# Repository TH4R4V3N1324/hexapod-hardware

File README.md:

# hexapod-hardware

Open-source hardware for 3D-printed six-legged walking robots. The repo has the CAD (STEP for editing, STL for printing), bills of materials, print lists and assembly docs. Shared electronics, including the [leg hub](electronics/leg-hub/) power and data board, are in [`electronics/`](electronics/).

## Variants

| Variant | Key hardware | Status |
|---|---|---|
| [Explorer](explorer/) | ST3215 servos, Raspberry Pi 5, lidar | v0.2, in development |

Each variant's folder has its own README, [print list](explorer/print-list.md), BOM and changelog.

## Licences

This repository uses two licences:

- **CAD, STLs and documentation**: [Creative Commons Attribution-ShareAlike 4.0 International (CC BY-SA 4.0)](LICENSE)
- **PCB designs** (everything in [`electronics/`](electronics/)): [CERN Open Hardware Licence Version 2 – Weakly Reciprocal (CERN-OHL-W-2.0)](electronics/LICENSE)

The source for this design is at <https://github.com/TH4R4V3N1324/hexapod-hardware>.

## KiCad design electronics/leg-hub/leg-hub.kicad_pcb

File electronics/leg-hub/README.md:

# Leg hub

> ⚠️ **v0.1: under development.** The design may change, and the board hasn't been fully verified. Check everything against the schematic before you power it up.

The leg hub is the power and data board for one side of the hexapod. Every robot uses **two identical boards**, one for the left legs and one for the right. Each board:

- **Distributes power and servo data to three legs** through individually fused connectors.
- **Makes 5 V / 5 A** for the Raspberry Pi, sensors and other peripherals.
- **Measures current, voltage and power** for its side with an INA226 on I²C.
- **Switches servo power** with a fail-safe high-side switch that needs both a GPIO enable and a closed kill loop.
- **Switches itself fully on and off** from one small latching switch.

## Specifications

| | |
|---|---|
| Input | 3S LiPo (9.0–12.6 V) via XT30 |
| Board switch | P-FET, about 15 A per board |
| Leg outputs | 3 × fused 5 A (mini blade), battery voltage |
| 5 V output | 5 A synchronous buck (TPS56528), 650 kHz |
| Current sense | INA226, 2 mΩ shunt, about 40 A full scale |
| Host logic | 3.3 V (default) or 5 V, selected by JP3 |
| Input protection | SMBJ13A TVS, 220 µF + 470 µF bulk |
| Mounting | 4 × M3 |

## How the board works

<p align="center">
  <picture>
    <source media="(prefers-color-scheme: dark)" srcset="images/power-flow-dark.png">
    
  </picture>
</p>

Servo data comes in on BUS_IN (J6) and is shared to the data pin of all three leg connectors.

1. **Board switch (Q3).** The board stays off until J11 is shorted. If the switch is open or a wire breaks, R18 turns Q3 off and everything on that board loses power: buck, Pi and servos. Only about 1 mA flows through the switch, so any small latching switch works.
2. **Current sense (U2, R1).** The shunt sits after Q3, so the INA226 measures everything the board draws: servos plus 5 V load.
3. **Servo switch (Q1).** Servo power comes on only when **SERVO_EN is high and the kill loop (J8) is closed**. R5 holds the servos off while the host GPIO floats during boot.
4. **Leg outputs.** Each leg has its own 5 A blade fuse, matched to the roughly 3 A-per-pin rating of the servo connectors (brief peaks are fine).
5. **Servo data.** Data from the bus servo adapter is shared to all three legs, each through a 22 Ω series resistor and an ESD clamp.
6. **Adapter power.** J6 pin 2 feeds the switched servo rail to the bus servo adapter through a Schottky diode (D7), to power the adapter's own chips. The diode stops the adapter feeding power back into the board. This feed isn't fused, so don't power servos or anything else through the adapter. Servo power goes to the legs only through J3–J5.

## Connectors

| Ref | Name | Type | Pinout / use |
|---|---|---|---|
| J1 | Battery in | Amass XT30PW-M | 3S pack. Check polarity against your lead. |
| J2 | 5 V out | Molex Micro-Fit 3.0, 2-pin | 5 V / 5 A for the Pi, sensors or other peripherals |
| J3–J5 | LEG1–LEG3 | Molex SPOX 5267-03A (2.5 mm) | 1 DATA · 2 V+ (fused) · 3 GND. Same pinout as the servos, so a straight-through servo cable works. |
| J6 | BUS_IN | Molex SPOX 5267-03A | To the bus servo adapter: 1 DATA · 2 V out to the adapter (servo rail through D7, for the adapter's chips only) · 3 GND |
| J7 | CTRL | JST PH, 5-pin | To the host (Pi / ESP32 / Pico / Arduino): 1 SDA · 2 SCL · 3 INA ALERT (open-drain) · 4 SERVO_EN · 5 GND |
| J8 | KILL | JST PH, 2-pin | Normally-closed kill loop. Open = servos off. |
| J9, J10 | QWIIC | JST SH, 4-pin | Qwiic / STEMMA QT: 1 GND · 2 3V3 · 3 SDA · 4 SCL. The two ports are wired in parallel for daisy-chaining. |
| J11 | PWR_SW | JST PH, 4-pin | Main switch and its light: 1–2 switch (short to turn the board on) · 3 LED+ · 4 LED− (GND). LED+ is live only while the board is on, through R20 (1 kΩ). |

## Jumpers

| Ref | Name | Default | Purpose |
|---|---|---|---|
| JP1 | ADDR | Open (left) / **bridged (right)** | INA226 address: open = `0x40`, bridged = `0x41` |
| JP2 | KILL_BYP | Open | Bypasses the kill loop. Use it on the bench only. |
| JP3 | LOGIC_V | Cap on 1–2 | INA226 logic level: 1–2 = 3.3 V host, 2–3 = 5 V host. Must be 1–2 when using Qwiic. |
| JP4 | QW_PWR | Open | Feeds Qwiic 3V3 from this board. Leave it open with a Pi, and bridge it only if nothing upstream powers the chain. |
| JP5 | I2C_PU | Open | On-board 4.7 kΩ I²C pull-ups. Leave them open with a Pi, which already has pull-ups. |
| JP6 | PWR_BYP | Open | Keeps the board always on, without a switch. Bench use only. |

## Left vs right board

The two boards are the same PCB. The only difference is the INA226 address, so both can share one I²C bus:

| | Left | Right |
|---|---|---|
| JP1 | Open → `0x40` | Bridged → `0x41` |

Either board's 5 V output can power the Pi or peripherals.

## Wiring the pair

- **Battery:** split the pack to both boards' J1 with **equal-length wires**.
- **Power switch:** wire one latching switch to **both boards' J11 pins 1–2 in parallel** for a single hard power-off. There's no soft shutdown.
- **Switch light:** wire an illuminated switch's LED, or any other indicator, to J11 pins 3 (+) and 4 (−) of **one** board. R20 (1 kΩ) suits a bare LED and keeps a shorted wire harmless. A 12 V-rated LED with its own resistor will light more dimly, so change R20 to a lower value or 0 Ω if you want it brighter.
- **E-stop:** use a button with two normally-closed contacts and wire one contact across each board's J8.
- **SERVO_EN:** drive it from a Pi GPIO that defaults to **pull-down at boot** (GPIO9–27), so the servos stay off while the Pi starts.
- **I²C:** chain Pi → left board → right board → IMU and so on, through J7 or the Qwiic ports.
- **Never tie the two 5 V rails together.** Watch for this through USB VBUS if the Pi and a USB device are powered from different boards.

## Before first power-up

- [ ] JP1 set correctly for left / right
- [ ] JP3 on 1–2 for a Pi or other 3.3 V host
- [ ] JP2, JP4, JP5 and JP6 open (unless you need them, as described above)
- [ ] XT30 and bus adapter cable pin 1 checked against your leads
- [ ] Fuses F1–F3 fitted (5 A mini blade)

## Files

| File | Contents |
|---|---|
| `leg-hub.kicad_pro` | KiCad project. Open this one. |
| `leg-hub.kicad_sch` | Schematic |
| `leg-hub.kicad_pcb` | PCB layout |
| `fp-lib-table`, `hexapod.pretty/` | Project footprint library (custom TDSON-8 footprint for Q3) |
| `3dmodels/` | 3D models for the XT30, Micro-Fit and SPOX connectors, and a simplified model of Q3's PG-TDSON-8 package |
| `images/` | Diagrams used in this README |

The project needs **KiCad 10** or newer. Every other symbol, footprint and 3D model comes from the standard KiCad libraries.

## Licence

CERN Open Hardware Licence v2, Weakly Reciprocal (CERN-OHL-W). See [`../LICENSE`](../LICENSE).

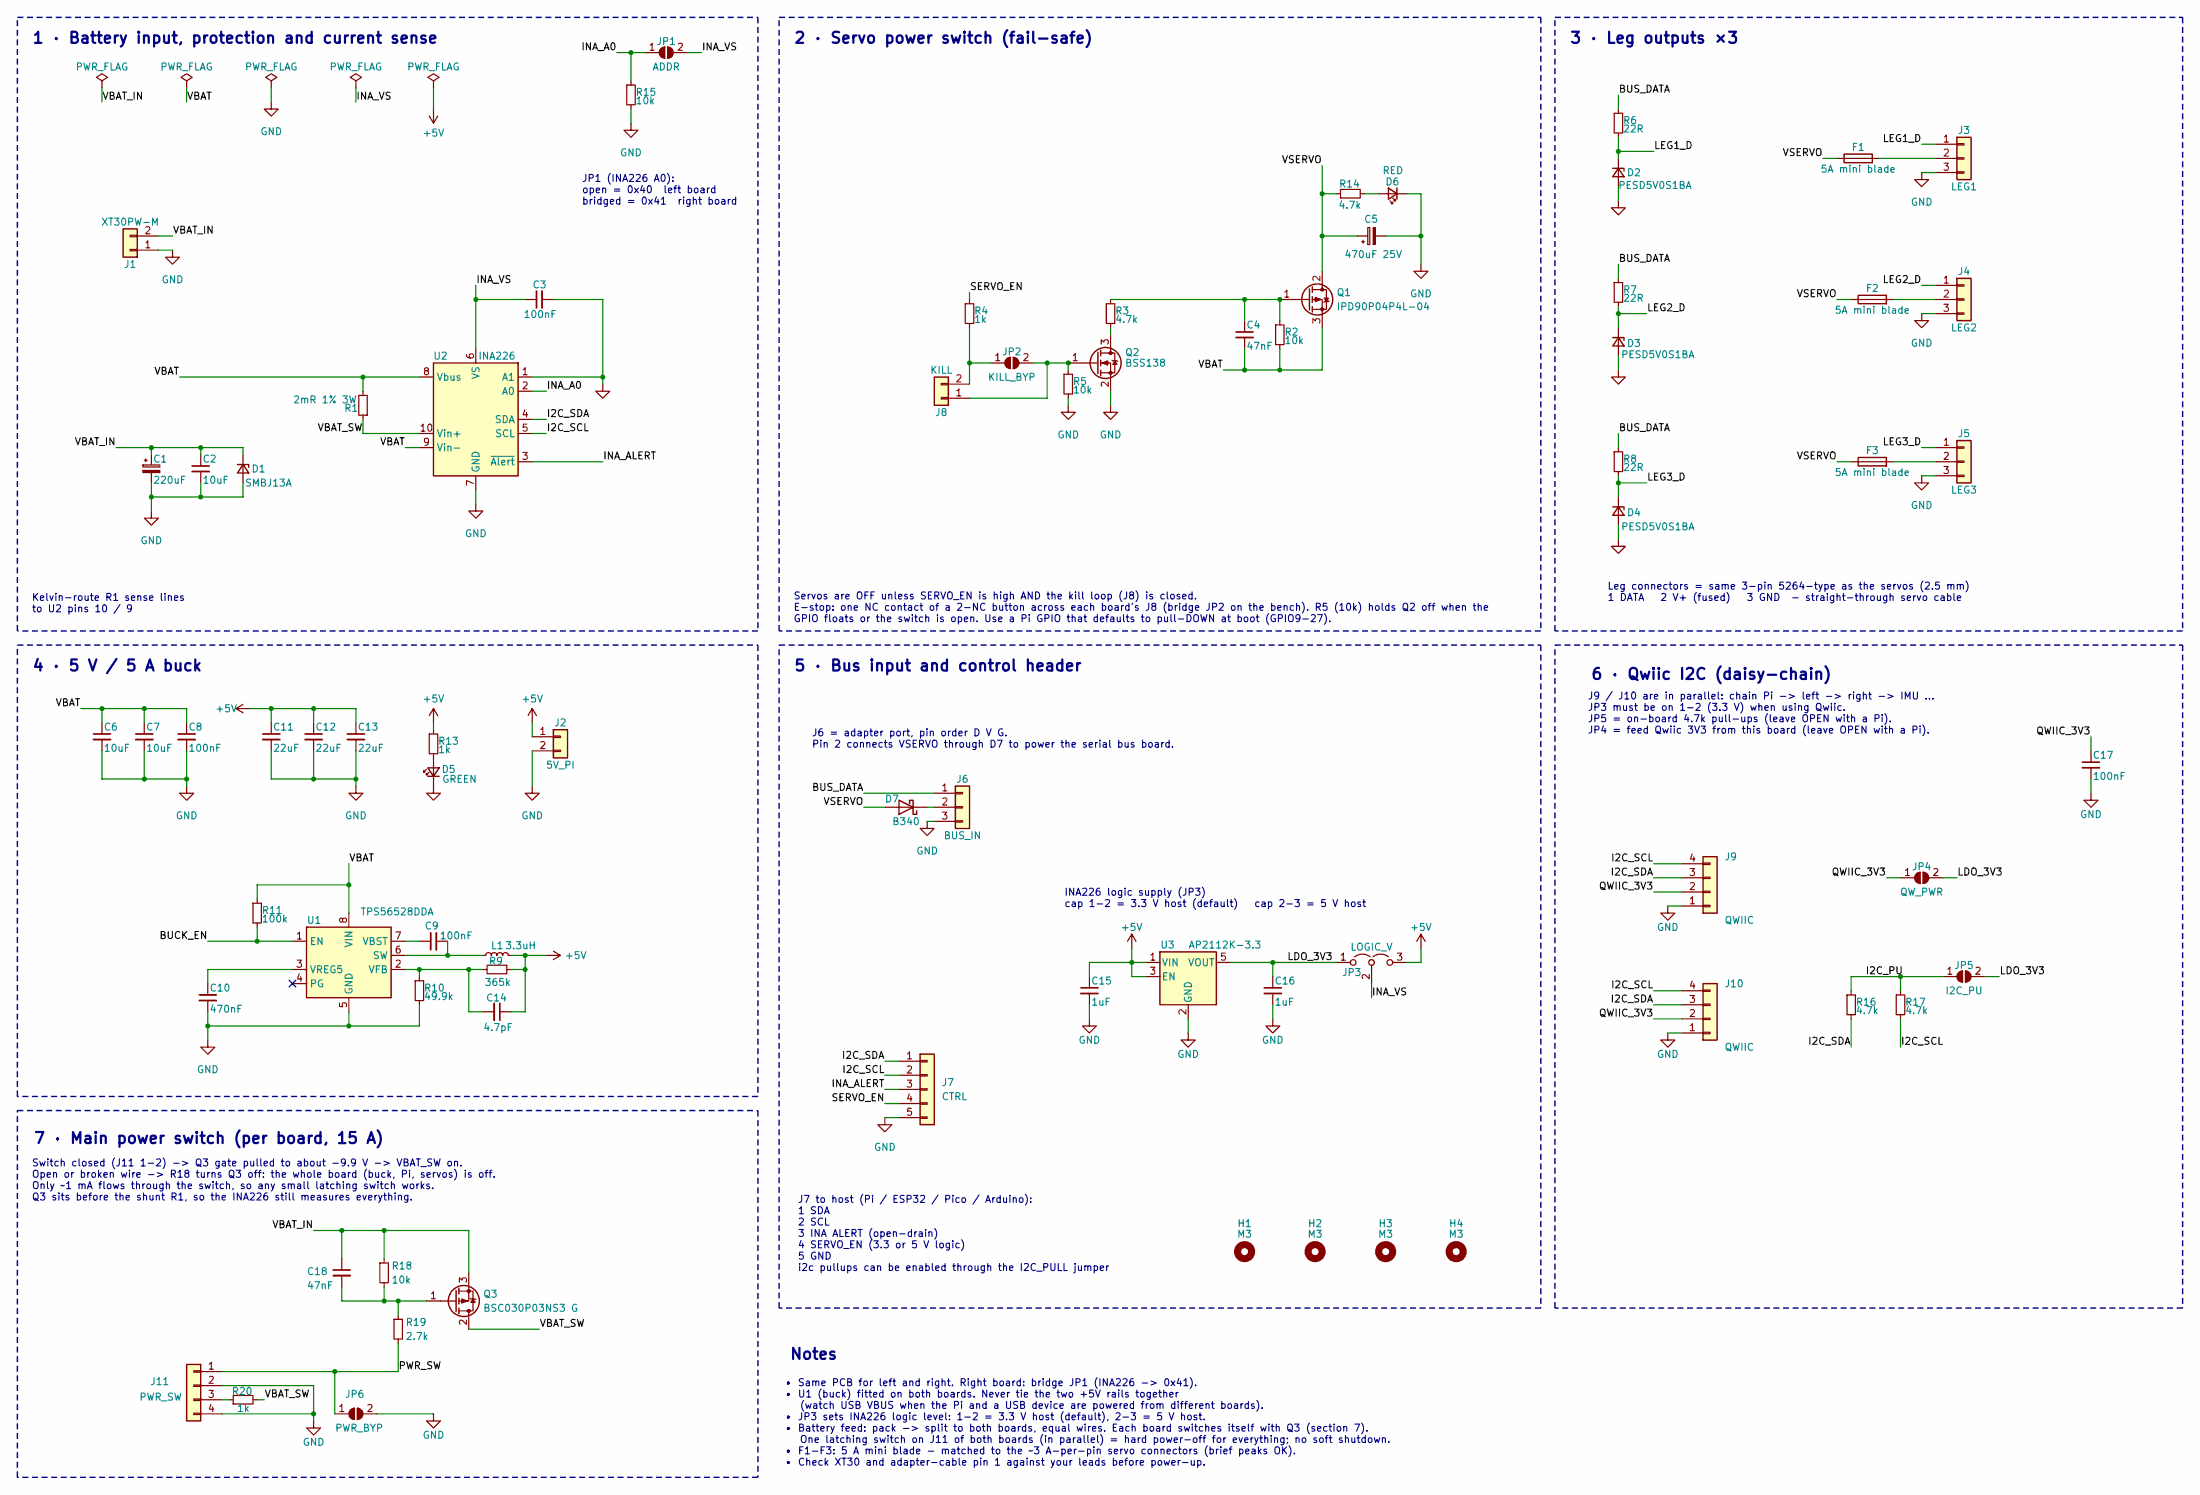
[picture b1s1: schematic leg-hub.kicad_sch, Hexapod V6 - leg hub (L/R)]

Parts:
C1: 220uF; CP_Elec_8x10.5
C2, C6, C7: 10uF; C_1206_3216Metric
C3, C8, C9, C17: 100nF; C_0603_1608Metric
C4, C18: 47nF; C_0603_1608Metric
C5: 470uF 25V; CP_Elec_10x10.5
C10: 470nF; C_0603_1608Metric
C11, C12, C13: 22uF; C_1206_3216Metric
C14: 4.7pF; C_0603_1608Metric
C15, C16: 1uF; C_0603_1608Metric
D1: SMBJ13A; D_SMB; MPN SMBJ13A
D2, D3, D4: PESD5V0S1BA; D_SOD-323; MPN PESD5V0S1BA
D5: GREEN; LED_0603_1608Metric
D6: RED; LED_0603_1608Metric
D7: B340; D_SMC
F1, F2, F3: 5A mini blade; Fuseholder_Blade_Mini_Keystone_3568; MPN Keystone 3568 + 5 A mini blade fuse
H1, H2, H3, H4: M3; MountingHole_3.2mm_M3
J1: XT30PW-M; AMASS_XT30PW-M_1x02_P2.50mm_Horizontal; MPN Amass XT30PW-M
J2: 5V_PI; Molex_Micro-Fit_3.0_43650-0200_1x02_P3.00mm_Horizontal; MPN Molex 43650-0200
J3: LEG1; Molex_SPOX_5267-03A_1x03_P2.50mm_Vertical; MPN Molex 5267-03A
J4: LEG2; Molex_SPOX_5267-03A_1x03_P2.50mm_Vertical; MPN Molex 5267-03A
J5: LEG3; Molex_SPOX_5267-03A_1x03_P2.50mm_Vertical; MPN Molex 5267-03A
J6: BUS_IN; Molex_SPOX_5267-03A_1x03_P2.50mm_Vertical; MPN Molex 5267-03A
J7: CTRL; JST_PH_S5B-PH-K_1x05_P2.00mm_Horizontal
J8: KILL; JST_PH_S2B-PH-K_1x02_P2.00mm_Horizontal; MPN JST S2B-PH-K-S
J9, J10: QWIIC; JST_SH_SM04B-SRSS-TB_1x04-1MP_P1.00mm_Horizontal; MPN JST SM04B-SRSS-TB(LF)(SN) (LCSC C160404)
J11: PWR_SW; JST_PH_S4B-PH-K_1x04_P2.00mm_Horizontal
JP1: ADDR; SolderJumper-2_P1.3mm_Open_RoundedPad1.0x1.5mm
JP2: KILL_BYP; SolderJumper-2_P1.3mm_Open_RoundedPad1.0x1.5mm
JP3: LOGIC_V; PinHeader_1x03_P2.54mm_Vertical
JP4: QW_PWR; SolderJumper-2_P1.3mm_Open_RoundedPad1.0x1.5mm
JP5: I2C_PU; SolderJumper-2_P1.3mm_Open_RoundedPad1.0x1.5mm
JP6: PWR_BYP; SolderJumper-2_P1.3mm_Open_RoundedPad1.0x1.5mm
L1: 3.3uH; L_Coilcraft_XAL7030-332; MPN Coilcraft XAL7030-332
Q1: IPD90P04P4L-04; TO-252-3_TabPin2; MPN IPD90P04P4L-04
Q2: BSS138; SOT-23; MPN BSS138
Q3: BSC030P03NS3 G; TDSON-8_GDS; MPN BSC030P03NS3 G
R1: 2mR 1% 3W; R_2512_6332Metric
R2, R5, R15, R18: 10k; R_0603_1608Metric
R3, R14, R16, R17: 4.7k; R_0603_1608Metric
R4, R13: 1k; R_0603_1608Metric
R6, R7, R8: 22R; R_0603_1608Metric
R9: 365k; R_0603_1608Metric
R10: 49.9k; R_0603_1608Metric
R11: 100k; R_0603_1608Metric
R19: 2.7k; R_0603_1608Metric
R20: 1k; R_1206_3216Metric
U1: TPS56528DDA; Texas_HSOP-8-1EP_3.9x4.9mm_P1.27mm_ThermalVias; MPN TPS56528DDAR
U2: INA226; TSSOP-10_3x3mm_P0.5mm; MPN INA226AIDGSR
U3: AP2112K-3.3; SOT-23-5

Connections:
+5V: C11.1, C12.1, C13.1, C14.1, C15.1, J2.1, JP3.3 (B), L1.2, R9.1, R13.1, U3.1 (VIN), U3.3 (EN)
/BUCK_EN: R11.2, U1.1 (EN)
/BUS_DATA: J6.1, R6.1, R7.1, R8.1
/I2C_PU: JP5.1 (A), R16.1, R17.1
/I2C_SCL: J7.2, J9.4, J10.4, R17.2, U2.5 (SCL)
/I2C_SDA: J7.1, J9.3, J10.3, R16.2, U2.4 (SDA)
/INA_A0: JP1.1 (A), R15.1, U2.2 (A0)
/INA_ALERT: J7.3, U2.3 (~Alert)
/INA_VS: C3.1, JP1.2 (B), JP3.2 (C), U2.6 (VS)
/LDO_3V3: C16.1, JP3.1 (A), JP4.2 (B), JP5.2 (B), U3.5 (VOUT)
/LEG1_D: D2.1 (K), J3.1, R6.2
/LEG2_D: D3.1 (K), J4.1, R7.2
/LEG3_D: D4.1 (K), J5.1, R8.2
/PWR_SW: J11.1, JP6.1 (A), R19.2
/QWIIC_3V3: C17.1, J9.2, J10.2, JP4.1 (A)
/SERVO_EN: J7.4, R4.1
/VBAT: C4.2, C6.1, C7.1, C8.1, Q1.3 (S), R1.2, R2.2, R11.1, U1.8 (VIN), U2.8 (Vbus), U2.9 (Vin-)
/VBAT_IN: C1.1, C2.1, C18.1, D1.1 (K), J1.2, Q3.3 (S), R18.1
/VBAT_SW: Q3.2 (D), R1.1, R20.2, U2.10 (Vin+)
/VSERVO: C5.1, D7.2 (A), F1.1, F2.1, F3.1, Q1.2 (D), R14.1
GND: C1.2, C2.2, C3.2, C5.2, C6.2, C7.2, C8.2, C10.2, C11.2, C12.2, C13.2, C15.2, C16.2, C17.2, D1.2 (A), D2.2 (A), D3.2 (A), D4.2 (A), D5.1 (K), D6.1 (K), J1.1, J2.2, J3.3, J4.3, J5.3, J6.3, J7.5, J9.1, J10.1, J11.2, J11.4, JP6.2 (B), Q2.2 (S), R5.2, R10.2, R15.2, U1.5 (GND), U1.9 (GND), U2.1 (A1), U2.7 (GND), U3.2 (GND)
unnamed: D5.2 (A), R13.2
unnamed: D6.2 (A), R14.2
unnamed: D7.1 (K), J6.2
unnamed: F1.2, J3.2
unnamed: F2.2, J4.2
unnamed: F3.2, J5.2
unnamed: J8.1, JP2.2 (B), Q2.1 (G), R5.1
unnamed: J8.2, JP2.1 (A), R4.2
unnamed: J11.3, R20.1
unnamed: C4.1, Q1.1 (G), R2.1, R3.1
unnamed: Q2.3 (D), R3.2
unnamed: C18.2, Q3.1 (G), R18.2, R19.1
unnamed: C9.2, L1.1, U1.6 (SW)
unnamed: C9.1, U1.7 (VBST)
unnamed: C14.2, R9.2, R10.1, U1.2 (VFB)
unnamed: C10.1, U1.3 (VREG5)

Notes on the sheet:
2 · Servo power switch (fail-safe)
4 · 5 V / 5 A buck
Kelvin-route R1 sense lines to U2 pins 10 / 9
1 · Battery input, protection and current sense
5 · Bus input and control header
Notes
7 · Main power switch (per board, 15 A)
Servos are OFF unless SERVO_EN is high AND the kill loop (J8) is closed. E-stop: one NC contact of a 2-NC button across each board's J8 (bridge JP2 on the bench). R5 (10k) holds Q2 off when the GPIO floats or the switch is open. Use a Pi GPIO that defaults to pull-DOWN at boot (GPIO9-27).
J6 = adapter port, pin order D V G. Pin 2 connects VSERVO through D7 to power the serial bus board.
JP1 (INA226 A0): open = 0x40 left board bridged = 0x41 right board
6 · Qwiic I2C (daisy-chain)
3 · Leg outputs ×3
Leg connectors = same 3-pin 5264-type as the servos (2.5 mm) 1 DATA 2 V+ (fused) 3 GND - straight-through servo cable
• Same PCB for left and right. Right board: bridge JP1 (INA226 -> 0x41). • U1 (buck) fitted on both boards. Never tie the two +5V rails together (watch USB VBUS when the Pi and a USB device are powered from different boards). • JP3 sets INA226 logic level: 1-2 = 3.3 V host (default), 2-3 = 5 V host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
INA226 logic supply (JP3) cap 1-2 = 3.3 V host (default) cap 2-3 = 5 V host
J9 / J10 are in parallel: chain Pi -> left -> right -> IMU ... JP3 must be on 1-2 (3.3 V) when using Qwiic. JP5 = on-board 4.7k pull-ups (leave OPEN with a Pi). JP4 = feed Qwiic 3V3 from this board (leave OPEN with a Pi).
Switch closed (J11 1-2) -> Q3 gate pulled to about -9.9 V -> VBAT_SW on. Open or broken wire -> R18 turns Q3 off: the whole board (buck, Pi, servos) is off. Only ~1 mA flows through the switch, so any small latching switch works. Q3 sits before the shunt R1, so the INA226 still measures everything.
J7 to host (Pi / ESP32 / Pico / Arduino): 1 SDA 2 SCL 3 INA ALERT (open-drain) 4 SERVO_EN (3.3 or 5 V logic) 5 GND i2c pullups can be enabled through the I2C_PULL jumper

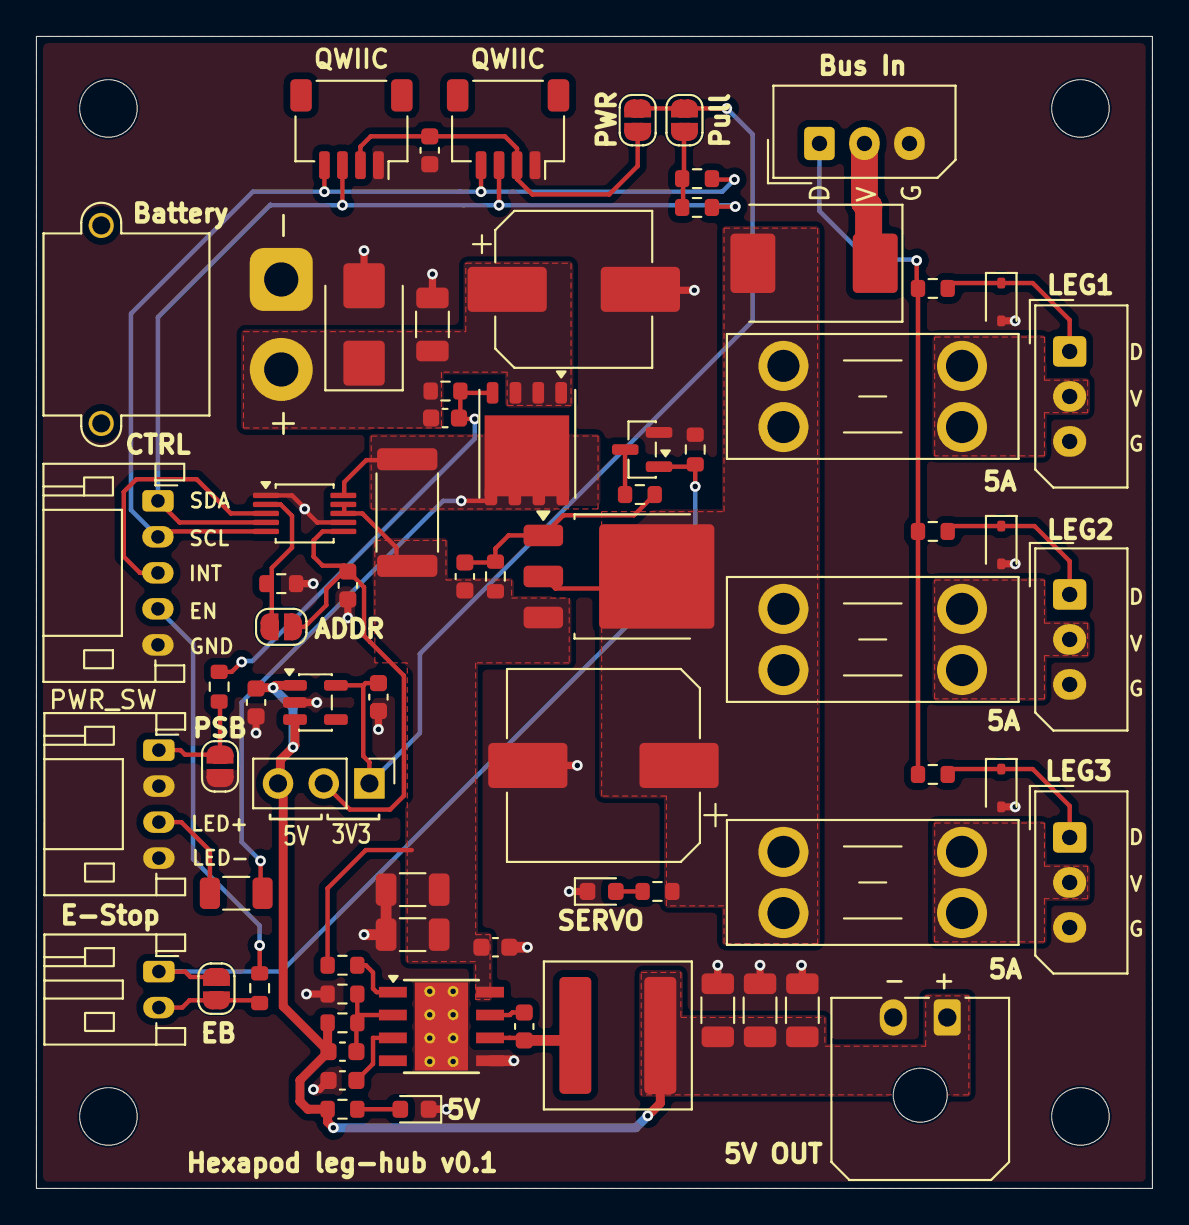
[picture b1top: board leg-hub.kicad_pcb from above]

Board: 2 copper layers, 62.0 x 64.0 mm, 75 parts (0 on the bottom side), 37 nets.
